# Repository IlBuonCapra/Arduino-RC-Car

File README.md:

# Arduino - RC Car
Arduino RC Car with nRF20L01 module, controlled by Syma X5C remote controller.
I used [Symaxrx Library](https://github.com/Suxsem/symaxrx) to control the car.

## PCB

I also created my personal shield for this projects using Eagle PCB.
Everything works with 12 volts from a battery packs made of six 18650 batteries.

A L298 Dual Full Bridge Driver is used to drive motors in each directions.
L298's enables are connected to 5 volts, so the motors are always ready to work.
If you want, you can short-circuit resistors R1,R2.
Unfortunaly, the steering motor is not controlled with PWM due to the reduced number of PWM pins of Arduino, but the car steers well.

12 volts leds are used like lights and a buzzer is used like clacson.

For this shield, i used the following pins:
| PIN | Function |
| --- | --- |
| 3 | CLACSON |
| 4 | LIGHTS |
| 5 | MOTOR1 |
| 6 | MOTOR2 |
| 7 | STEERING1 |
| 8 | STEERING2 |
| 9 | NRF_CE |
| 10 | NRF_CSN |
| 11 | NRF_MOSI |
| 12 | NRF_MISO |
| 13 | NRF_SCK |

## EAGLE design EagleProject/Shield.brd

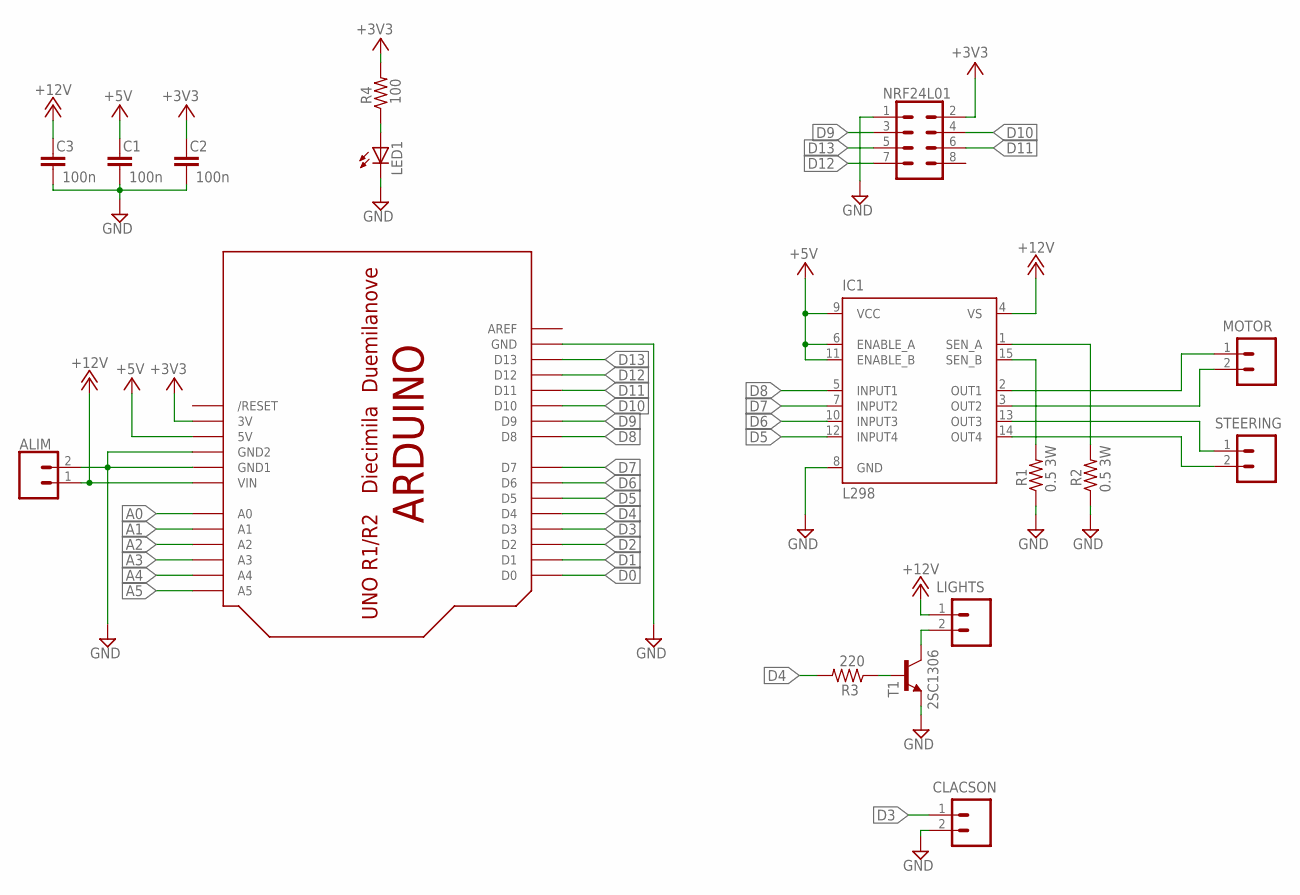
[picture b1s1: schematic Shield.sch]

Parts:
ALIM: CONN_025MM; SCREWTERMINAL-5MM-2
C1, C2, C3: 100n; C5B2.5
CLACSON: CONN_025MM; SCREWTERMINAL-5MM-2
IC1: L298; MULTIWATT-15
LED1: LED5MM
LIGHTS: CONN_025MM; SCREWTERMINAL-5MM-2
MOTOR: CONN_025MM; SCREWTERMINAL-5MM-2
NRF24L01: CONN_04X2; 2X4
R1, R2: 0.5 3W; 0309/12
R3: 220; 0309/12
R4: 100; 0309/12
STEERING: CONN_025MM; SCREWTERMINAL-5MM-2
T1: 2SC1306; TO220BV
U$1: ARDUINO-NOHOLE

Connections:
+3V3: C2.1, NRF24L01.2, R4.2, U$1.3V
+5V: C1.1, IC1.6 (ENABLE_A), IC1.9 (VCC), IC1.11 (ENABLE_B), U$1.5V
+12V: ALIM.1, C3.1, IC1.4 (VS), LIGHTS.1, U$1.VIN
A0: U$1.A0
A1: U$1.A1
A2: U$1.A2
A3: U$1.A3
A4: U$1.A4
A5: U$1.A5
BASE: R3.1, T1.1 (B)
COL: LIGHTS.2, T1.2 (C)
D0: U$1.D0
D1: U$1.D1
D2: U$1.D2
D3: CLACSON.1, U$1.D3
D4: R3.2, U$1.D4
D5: IC1.12 (INPUT4), U$1.D5
D6: IC1.10 (INPUT3), U$1.D6
D7: IC1.7 (INPUT2), U$1.D7
D8: IC1.5 (INPUT1), U$1.D8
D9: NRF24L01.3, U$1.D9
D10: NRF24L01.4, U$1.D10
D11: NRF24L01.6, U$1.D11
D12: NRF24L01.7, U$1.D12
D13: NRF24L01.5, U$1.D13
GND: ALIM.2, C1.2, C2.2, C3.2, CLACSON.2, IC1.8 (GND), LED1.K (C), NRF24L01.1, R1.1, R2.1, T1.3 (E), U$1.GND, U$1.GND1, U$1.GND2
unnamed: IC1.15 (SEN_B), R1.2
unnamed: LED1.A, R4.1
unnamed: IC1.3 (OUT2), MOTOR.2
unnamed: IC1.2 (OUT1), MOTOR.1
unnamed: IC1.13 (OUT3), STEERING.1
unnamed: IC1.14 (OUT4), STEERING.2
unnamed: IC1.1 (SEN_A), R2.2

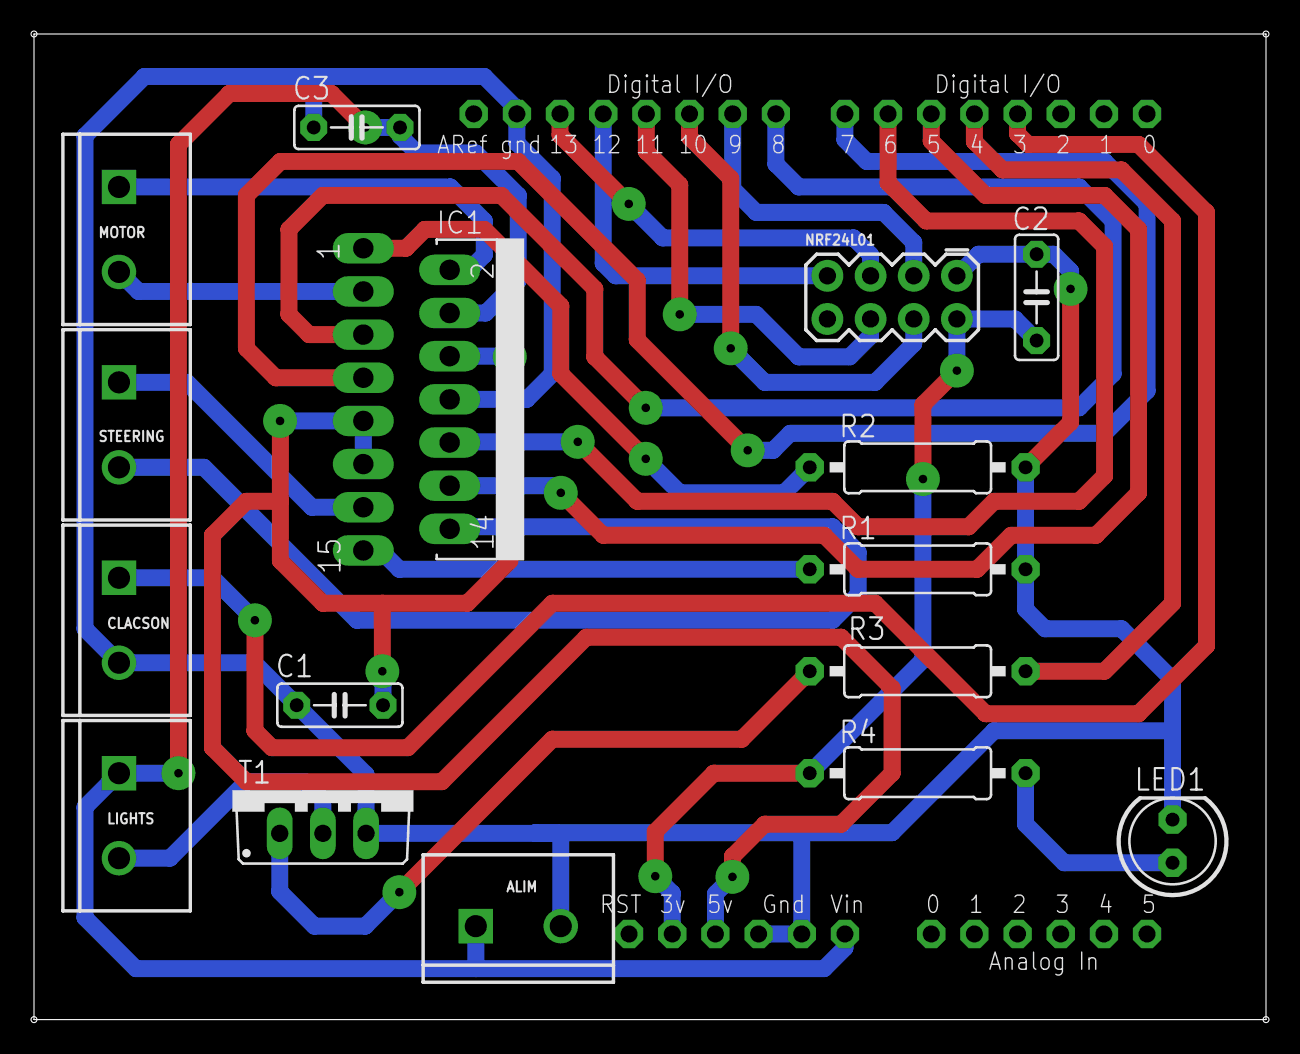
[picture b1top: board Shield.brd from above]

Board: 2 copper layers, 72.5 x 58.0 mm, 17 parts (0 on the bottom side), 24 nets.

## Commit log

2020-05-28 Update README.md
    Added description of project

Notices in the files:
parts and their libraries:
SparkFun-Connectors: Licensing: Creative Commons ShareAlike 4.0 International - https://creativecommons.org/licenses/by-sa/4.0
